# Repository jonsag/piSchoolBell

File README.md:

# piSchoolBell

This runs a Raspberry Pi as a controller for a school bell.  
It makes the school bell ring at the right times taking the calendar into consideration.  
Also there is an LCD screen to visualize time, database stats, upcoming rings etc.  

Administration of the school bell is done via a web UI.  

It is written entirely in python.  

Also it installs gpio-watch to catch the buttons connected to the Pi's GPIO. [https://github.com/larsks/gpio-watch](https://github.com/larsks/gpio-watch)  

## Updates

### 3/7 -22

Now running on RaspberryPiOS Bullseye.  
Everything updated to run on python3.  
Updated install script.  
Made it easier for those not having the Swedish holidays. (More work needed...)  
New module for printing to LCD.  
Fixed apache not defaulting to index.py.  

### 30/6 -22

The API for Swedish holidays, api.dryg.net, is dead.  
Substituted by [sholiday.faboul.se](https://sholiday.faboul.se/dagar/).  

### 7/3 -20

Changed all GPIO pins to make an easier PCB layout possible.  
This makes all older electric installs incompatible.  
Added KiCad files for new pin layout.  

Corrected editing of ring times.  

### 6/3 -20

Bug discovered  
There was a fault in the database setup.  
Instead of updating, you can:  
Log in to database  
>$ sudo mysql -u root -p piSchoolBell  

Change column type  
>MariaDB [piSchoolBell]> ALTER TABLE ringTimes CHANGE weekDays weekDays VARCHAR(7);  

## Hardware setup

### Parts list

* 1 x Raspberry Pi 3 B+, kjell.com Art#88100 (could be any of the later models)  
* 1 x LCD display, kjell.com Art#90215 (16x2 characters, based on the HD44780 chip)  
* 1 x USB micro power adapter, kjell.com Art#88525  
* 1 x Micro SD card, kjell.com Art#97600  
* 1 x 10k potentiometer, kjell.com Art#90633  
* 1 x 5V relay module, kjell.com Art#87878  
* 4 x Push button, kjell.com Art#36023  
* 4 x 10k resistor  
* 4 x 1k resistor  
* 1 x Switch, kjell.com Art#36016  
* 1 x Casing for rpi, kjell.com Art#89030  
* 1 x Casing for relay, kjell.com Art#89014  
* 1 x RTC-module, kjell.com Art#87984  
* 1 x CR2032 battery, kjell.com ART#33715  
* GPIO header connector, kjell.com Art#87915 (or breakout board)  
* Wiring, cables  
* PCB board, kjell.com Art#89416 or Art#89435 (or a breadboard, just to set it up)  

* Soldering material  

### The build  

Assemble all the parts according to the KiCad files.  

### Install and configure OS

Download RaspberryPiOS Lite from [https://www.raspberrypi.com/software/operating-systems/](https://www.raspberrypi.com/software/operating-systems/).  

Cd to where your download is.  
>$ xz -d 2022-04-04-raspios-bullseye-armhf-lite.img.xz  

Insert SD-card and find out drive letter.  
>$ dmesg  

For example '/dev/mmcblk0' or '/dev/sdb'.  

Unmount if mounted.  
>$ umount /dev/mmcblk0p1  
>$ umount /dev/mmcblk0p2  

Write image to SD-card.  
>$ sudo dd bs=4M if=2022-04-04-raspios-bullseye-armhf-lite.img of=/dev/mmcblk0 conv=fsync status=progress  

Remove SD-card and insert it again to make new partitions visible.  

Mount the first partition.  
>$ sudo mount /dev/mmcblk0p1 /mnt/tmp  

Write empty file to boot partition to enable ssh at boot.  
>$ sudo touch /mnt/tmp/ssh  

Unmount.  
>$ sudo umount /mnt/tmp  

Remove SD-card and insert it in a RPi connected to your local network and boot it up.  

### RPi configuration

For this version of the operating system you should have a monitor and keyboard hooked up at the first boot.  

After some restarts you will start to configure your machine:

* Select keyboard layout  
* Create user and set password. For the sake of this installation it's preferred you set 'pi' as username.  

After this you will have a prompt.  
Find out the ip of the RPi

>$ ifconfig

Connect to the RPi via ssh on another machine (if you don't want to continue as before).  

>$ ssh -ip from above-  -l pi  

Login with the username and password you created earlier  

### Configure

>$ sudo raspi-config  

1 S1    Configure wifi  
2 S4    Change hostname  
4 P2    Set GPU memory to 16  
5 L1    Set locales  
5 L2    Set time zone  
6 A1    Expand file system to use whole SD-card  

Reboot to set new options.  

### Update OS

Connect again  

>$ sudo apt-get update && sudo apt-get upgrade  

## Installation

### Install git

>$ sudo apt-get install git  

### Clone repository

>$ cd /home/pi  
>$ git clone <https://github.com/jonsag/piSchoolBell.git>  

### Run install script

>$ cd /home/pi/piSchoolBell  
>$ sudo ./install.sh  

### Initialize mysql (mariadb)

>$ sudo mysql_secure_installation  

Set root password, and press 'enter' on all other questions

### Create database

>$ sudo /home/pi/piSchoolBell/mysql-setup.sh  

### Add test data, if wanted (otherwise some things will act funny until you create your own entries)  

>$ /home/pi/piSchoolBell/insertTestData.sh  

### Download (Swedish) dates

>$ /home/pi/bin/piSchoolBell/getCalendar.py -v  

### For those living outside of Sweden

If you're not lucky enough to live in Sweden, you can run this to make all weekdays workdays.  

>$ /home/pi/piSchoolBell/makeAllWeekdaysToWorkdays.sh

This includes ALL Mondays to Fridays.  

You will have to manually add your own work free weekdays.  

To set 4'th of July 2023 to work free day (if it wasn't a Sunday already...)  
Connect to mysql  

>$ mysql -u pi -p$(grep password /home/pi/bin/piSchoolBell/mysql-config.ini | awk '{ print $3 }') piSchoolBell
>
>MariaDB [piSchoolBell]> UPDATE days SET isWorkDay = '0' WHERE date = '2023-06-04';

#### Note

In Sweden we use the correct way for dates and numbering days.  

The first day of the week is Monday. It has number '0' in the database.  
When printing dates we use 'YYYY-MM-DD'.  

### Make web pages secure

>$ sudo /home/pi/piSchoolBell/www-secure-setup.sh  

## If you're adding an RTC module

### Enable i2c

>$ sudo raspi-config  

3 I5    Enable I2C interface  

>$ ./install-rtc.sh  

### Set hardware clock

Check that time and date is correct  

>$ date  

Set hardware clock  

>$ sudo hwclock -w  

Comment out the following lines in /lib/udev/hwclock-set  

    if [ -e /run/systemd/system ] ; then  
        exit 0  
    fi  

Reboot  

## Configuration

Press button on unit to display its IP-address on the second line of the LCD.  
Connect to the unit by pointing your browser to  

    http://\<IP-address\>:8080'.  

Edit or add breaks, ring times and ring patterns.  

Remember, you can't really add rings on saturdays or sundays, as this is mainly intended for use on normal school schedules.  

### Automatic tasks

At the first of every month cron will download calendar from 'dryg.net', adding data to the database.  
Every night cron will delete past breaks and days from the database.  

## Usage

Normally the LCD display shows:  
Line 1: HH:MM YYYY-mm-dd, current time and date  
Line 2: HH:MM YYYY-mm-dd, the time and date for the next bell ring  

By pressing button 1, display will show:  
&nbsp;&nbsp;&nbsp;&nbsp;Line 1: days left in db, last date in db  
&nbsp;&nbsp;&nbsp;&nbsp;Line 2: IP-address  
&nbsp;&nbsp;&nbsp;&nbsp;&nbsp;&nbsp;&nbsp;&nbsp;If it shows 'Not connected' it has not been able to acquire an IP address.  
&nbsp;&nbsp;&nbsp;&nbsp;&nbsp;&nbsp;&nbsp;&nbsp;The first character on line 2 shows if the unit can access internet.  
&nbsp;&nbsp;&nbsp;&nbsp;&nbsp;&nbsp;&nbsp;&nbsp;If it is a '*' it is connected.  
&nbsp;&nbsp;&nbsp;&nbsp;&nbsp;&nbsp;&nbsp;&nbsp;If it is a '-' it is not connected.  

Pressing button 2 will make the LCD go back to showing default info.  

## USE THE BELOW WITH CAUTION, NOT TESTED ENOUGH

To dump database and logs to USB-stick:  
Format a stick to fat32 and label it 'PISCHOOLBEL'.  
Insert into Pi.  
&nbsp;&nbsp;&nbsp;&nbsp;Display will show:  
&nbsp;&nbsp;&nbsp;&nbsp;&nbsp;&nbsp;&nbsp;&nbsp;The USBs label and drive letter  
&nbsp;&nbsp;&nbsp;&nbsp;&nbsp;&nbsp;&nbsp;&nbsp;'USB mounted'  
Press button 3.  
&nbsp;&nbsp;&nbsp;&nbsp;Display will confirm writing  
&nbsp;&nbsp;&nbsp;&nbsp;When finished display shows number of files written  

Remove USB  
&nbsp;&nbsp;&nbsp;&nbsp;Display will show:  
&nbsp;&nbsp;&nbsp;&nbsp;&nbsp;&nbsp;&nbsp;&nbsp;drive letter  
&nbsp;&nbsp;&nbsp;&nbsp;&nbsp;&nbsp;&nbsp;&nbsp;'USB umounted'  

Edit the database file with the highest date and time on the stick.  
To read back edited file to database:  
Insert the USB-stick.  
&nbsp;&nbsp;&nbsp;&nbsp;Display will show:  
&nbsp;&nbsp;&nbsp;&nbsp;&nbsp;&nbsp;&nbsp;&nbsp;The USBs label and drive letter  
&nbsp;&nbsp;&nbsp;&nbsp;&nbsp;&nbsp;&nbsp;&nbsp;'USB mounted'  
Press button 4.  
&nbsp;&nbsp;&nbsp;&nbsp;Display will confirm reading  
&nbsp;&nbsp;&nbsp;&nbsp;...  
Not implemented yet.  
For now it only shows how many lines to read back to the database.  

## Issues

If you get problems with Adafruit_Python_CharLCD failing to write to LCD.  

>$ cd /home/pi/piSchoolBell/Adafruit_Python_CharLCD  
>$ sudo python setup.py install  

## Hardware clock / RTC, quick reference

Check system time:  

>$ date  

Check HW-time:  

>$ sudo hwclock -r  

Set HW-clock to system time:  

>$ sudo hwclock -w  

Set system clock from HW-clock:  

>$ sudo hwclock -s  

Set system date manually:  

>$ date +%Y%m%d -s "20120418"  

Set system time manually:  

>$ date +%T -s "11:14:00"  

Set HW-clock manually:  

>$ sudo hwclock --set --date="2011-08-14 16:45:05"  

## Below is only for my own convenience during programming of this project

>$ rsync -raci ~/Documents/EclipseWorkspace/piSchoolBell/* pi@192.168.10.44:/home/pi/bin/piSchoolBell/  
>$ rsync -raci ~/Documents/EclipseWorkspace/piSchoolBell/www/* pi@192.168.10.44:/var/www/piSchoolBell/  
>$ ssh pi@192.168.10.44 'sudo chmod 755 -R /var/www/piSchoolBell'  
>$ ssh pi@192.168.10.44 'sudo chown -R pi:www-data /var/www/piSchoolBell'  
>$ rsync -raci ~/Documents/EclipseWorkspace/piSchoolBell/purgeDatabase.py pi@192.168.10.44:/home/pi/bin/piSchoolBell/  
>
>$ rsync -raci ~/Documents/CodeWorkspace/piSchoolBell pi@192.168.10.99:/home/pi/  
>$ rsync -raci ~/Documents/CodeWorkspace/piSchoolBell/bin/* pi@192.168.10.99:/home/pi/bin/piSchoolBell  

### Things to check after install

>$ list /home/pi/bin/piSchoolBell/  
>$ cat /home/pi/bin/piSchoolBell/gpio.service  
>$ cat /lib/systemd/system/gpio.service  
>$ list /home/pi/bin/piSchoolBell/gpio-scripts  
>$ cat /home/pi/bin/piSchoolBell/gpio-scripts/gpio-script  
>$ list /var/www/piSchoolBell  
>$ cat etc/cron.d/piSchoolBell  
>$ ps ax | grep gpio  

### Run some tests

>$ /home/pi/bin/piSchoolBell/printToLcd.py -v  
>$ i2cdetect -y 1  
>$ cat /proc/driver/rtc

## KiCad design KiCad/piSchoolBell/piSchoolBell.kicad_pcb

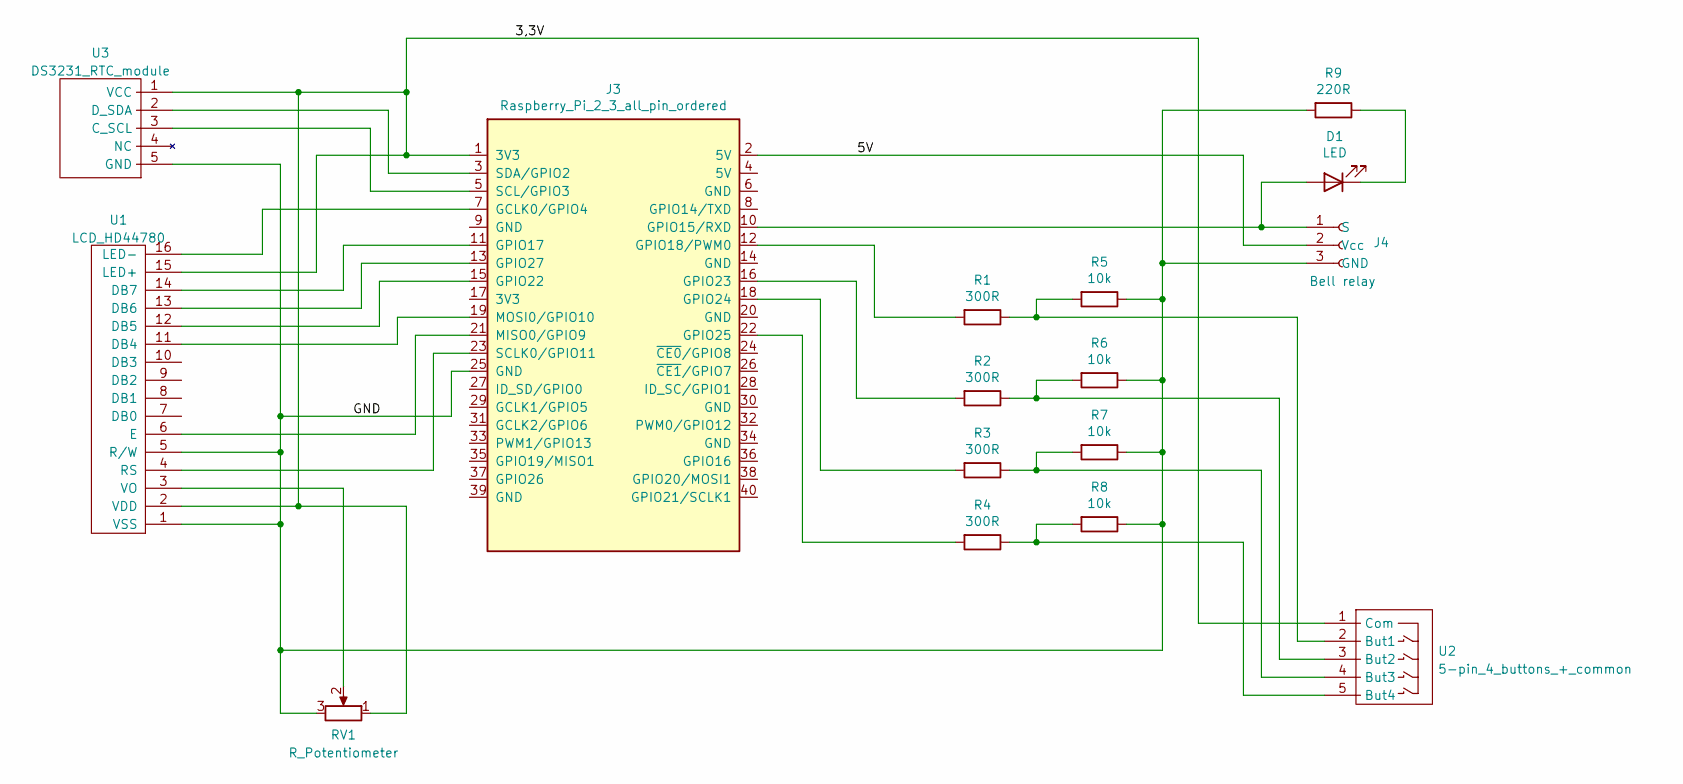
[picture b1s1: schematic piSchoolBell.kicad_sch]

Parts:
D1: LED; LED_D5.0mm_larger_pads
J3: Raspberry_Pi_2_3_all_pin_ordered; RaspberryPi_3b+_Hat_large
J4: Bell relay; 3-pin JST KY-019 relay
R1, R2, R3, R4: 300R; R_Axial_DIN0207_L6.3mm_D2.5mm_P10.16mm_Horizontal_larger_pa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
R5, R6, R7, R8: 10k; R_Axial_DIN0207_L6.3mm_D2.5mm_P10.16mm_Horizontal_larger_pa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
R9: 220R; R_Axial_DIN0207_L6.3mm_D2.5mm_P10.16mm_Horizontal_larger_pa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
RV1: R_Potentiometer; Potentiometer_Bourns_3339P_Vertical_large
U1: LCD_HD44780; LCD_HD44780_16x2_w_headers_large
U2: 5-pin_4_buttons_+_common; 5-pin JST 4 buttons + common
U3: DS3231_RTC_module; DS3231_RTC_module_large

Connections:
/3,3V: J3.1 (3V3), RV1.1, U1.2 (VDD), U1.15 (LED+), U2.1 (Com), U3.1 (VCC)
/5V: J3.2 (5V), J4.2 (Vcc)
/GND: J3.25 (GND), J4.3 (GND), R5.1, R6.1, R7.1, R8.1, R9.2, RV1.3, U1.1 (VSS), U1.5 (R/W), U3.5 (GND)
unnamed: D1.1 (K), R9.1
unnamed: D1.2 (A), J3.10 (GPIO15/RXD), J4.1 (S)
unnamed: J3.3 (SDA/GPIO2), U3.2 (D_SDA)
unnamed: J3.5 (SCL/GPIO3), U3.3 (C_SCL)
unnamed: J3.7 (GCLK0/GPIO4), U1.16 (LED-)
unnamed: J3.11 (GPIO17), U1.14 (DB7)
unnamed: J3.12 (GPIO18/PWM0), R1.2
unnamed: J3.13 (GPIO27), U1.13 (DB6)
unnamed: J3.15 (GPIO22), U1.12 (DB5)
unnamed: J3.16 (GPIO23), R2.2
unnamed: J3.18 (GPIO24), R3.2
unnamed: J3.19 (MOSI0/GPIO10), U1.11 (DB4)
unnamed: J3.21 (MISO0/GPIO9), U1.6 (E)
unnamed: J3.22 (GPIO25), R4.2
unnamed: J3.23 (SCLK0/GPIO11), U1.4 (RS)
unnamed: R1.1, R5.2, U2.2 (But1)
unnamed: R2.1, R6.2, U2.3 (But2)
unnamed: R3.1, R7.2, U2.4 (But3)
unnamed: R4.1, R8.2, U2.5 (But4)
unnamed: RV1.2, U1.3 (VO)

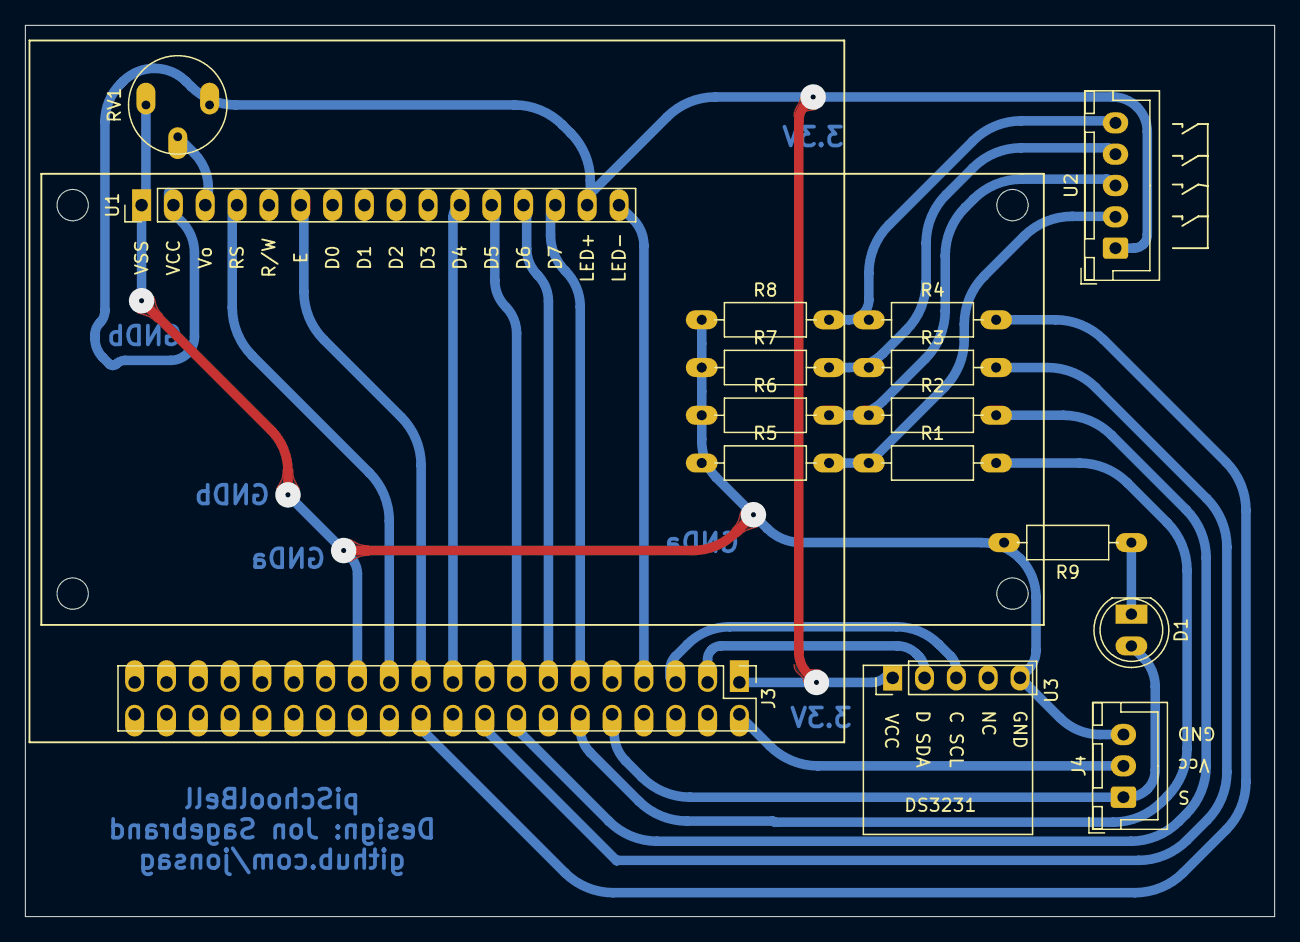
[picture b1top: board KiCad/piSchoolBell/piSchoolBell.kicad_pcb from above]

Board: 2 copper layers, 99.7 x 71.1 mm, 16 parts (0 on the bottom side), 23 nets.

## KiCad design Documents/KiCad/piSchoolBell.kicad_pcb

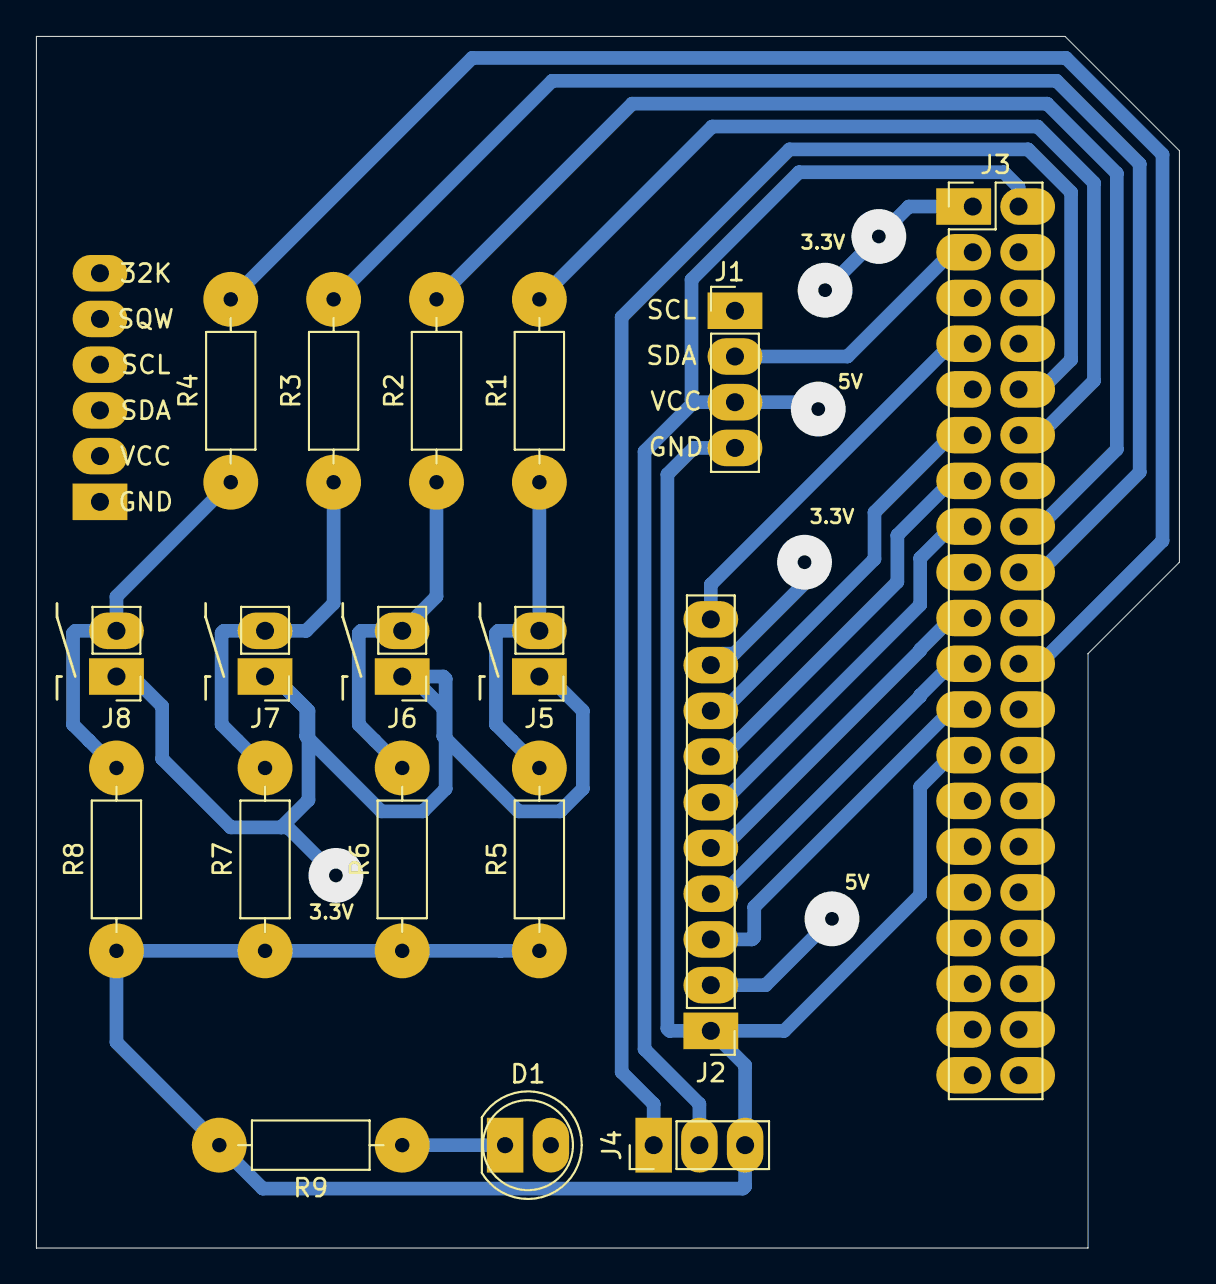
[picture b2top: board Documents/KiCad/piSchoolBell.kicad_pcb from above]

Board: 2 copper layers, 63.5 x 67.3 mm, 18 parts (0 on the bottom side), 22 nets.

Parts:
D1: LED; LED_D5.0mm_larger_pads
J1: ZS-042_4-pin_RTC_Module; ZS-042_RTC_Module_larger_pads
J2: 10-pin_header_LCD_interface; 10-pin_LCD_header_larger_pads
J3: Raspberry_Pi_2_3_all_pin_ordered; RaspberryPi_Hat_2x20_pin_GPIO_larger_pads
J4: 3-pin_KY-019_relay_header; 3-pin_KY-019_Relay_header_larger_pads
J5, J6, J7, J8: 2-pin_NO_switch_header; 2-pin_NO_switch_header_larger_pads
R1, R2, R3, R4: 300R; R_Axial_DIN0207_L6.3mm_D2.5mm_P10.16mm_Horizontal_larger_pa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
R5, R6, R7, R8: 10k; R_Axial_DIN0207_L6.3mm_D2.5mm_P10.16mm_Horizontal_larger_pa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
R9: 220R; R_Axial_DIN0207_L6.3mm_D2.5mm_P10.16mm_Horizontal_larger_pa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

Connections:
unnamed: D1.1, R9.1
unnamed: D1.2, J3.10, J4.1
unnamed: J1.1, J3.5
unnamed: J1.2, J3.3
unnamed: J1.3, J2.2, J3.2, J4.2
unnamed: J1.4, J2.1, J3.25, J4.3, R5.1, R6.1, R7.1, R8.1, R9.2
unnamed: J2.3, J3.23
unnamed: J2.4, J3.21
unnamed: J2.5, J3.19
unnamed: J2.6, J3.15
unnamed: J2.7, J3.13
unnamed: J2.8, J3.11
unnamed: J2.9, J3.1, J5.1, J6.1, J7.1, J8.1
unnamed: J2.10, J3.7
unnamed: J3.12, R1.2
unnamed: J3.16, R2.2
unnamed: J3.18, R3.2
unnamed: J3.22, R4.2
unnamed: J5.2, R1.1, R5.2
unnamed: J6.2, R2.1, R6.2
unnamed: J7.2, R3.1, R7.2
unnamed: J8.2, R4.1, R8.2

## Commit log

2018-03-05 Added first python code
2018-03-05 Starting to get calendar events from dryg.net
2018-03-05 Added a start to mysql setup
2018-03-06 Now gets and inserts school days i db
2018-03-07 Now rings bell at correct times and dates
2018-03-08 Now we have apache with in the game
2018-03-09 Now takes extra school days in concern
2018-03-09 Added test data
2018-03-09 Now edits ring patterns
2018-03-10 Now check ring patterns for illegal new entries
2018-03-11 Now we can view and add ring times
2018-03-11 Forgot...
2018-03-11 Now stops used ring patterns from being deleted
2018-03-11 Now we can edit school breaks
2018-03-11 Now displays upcoming ringtimes
2018-03-11 Changed some output on times
2018-03-11 Visual changes
2018-03-12 Prints IP to LCD when pressing button
2018-03-13 GPIO working. Deleted day_name. Created install script.
2018-03-13 Updated install
2018-03-13 Debugging
2018-03-13 My mistake
2018-03-13 New test data. Updated install
2018-03-13 Started on a purge to clean database
2018-03-14 Many updates. Almost done
2018-03-14 Changed web layouts
2018-03-14 More info on status
2018-03-15 Perhaps this would be v1.0b...
2018-03-15 Added file
2018-03-15 Fixed IP detection
2018-03-16 Moved files
2018-03-16 New readme and functions
2018-03-16 Added Documents
2018-03-17 Changed mysql setup
2018-03-17 Started to work on another way to edit the database
2018-03-18 Added scripts for auto mounting USB. Added uninstall.
2018-03-18 Changed permissions on automount
2018-03-18 Moved stuff around
2018-03-19 Now prints to LCD on USB insertion/removal
2018-04-17 Added two more buttons
2018-04-17 Added internet check
2018-04-18 Renamed file. Added dump/read USB
2018-04-18 Updated gpio files
2018-04-18 New install script
2018-04-18 Added RTV install
2018-04-18 Changed format on install
2018-04-18 Converted to dos
2018-04-18 Install dies on any error
2018-04-18 New install
2018-04-18 Finally managed to get RTC working?...
2018-04-18 Added and deleted files. Updated fritzing
2018-04-18 Changed permissions
2018-04-18 Updated fritz
2018-04-19 Many updates
2018-04-25 Added ringbell cron
2018-04-25 Reverted
2018-04-25 Added cron to ring bell
2019-12-21 Added Eagle schematics
2019-12-21 Routed PCB
2019-12-21 Coppper pour on pdfs
2019-12-22 Changed AuthName
2020-03-02 restored file that was deleted by mistake
2020-03-02 realized after viewing install.sh that it was supposed to be deleted...
2020-03-06 fixes bug in database setup
2020-03-06 escaped $ in install to put logs on right place
2020-03-07 fixed updating of ring times concerning ringpattern and weekdays
2020-03-07 new GPIO pins, eagle cad no longer relevant
2020-03-07 all new pin layout, check README!
2020-03-08 kicad
2020-03-08 moved pin for backlight in KiCad
2021-01-30 formatting
2021-04-21 formatted code
2021-11-04 some problem with formatting on last commit
2021-11-04 modules.py is back. Formats
2021-11-04 rm .gitignore
2022-05-17 kicad6
2022-06-12 minor schematic change
2022-06-30 api address changed
2022-07-01 python3 shebang
2022-07-01 formatting code, deleted deprecated library
2022-07-01 deleted Eagle and Fritzing
2022-07-01 lost a citation in uninstall
2022-07-02 sterted work on RPiOS
2022-07-03 seems to work now
2022-07-03 README
2022-07-03 htaccess
2022-07-04 run install.sh extra
